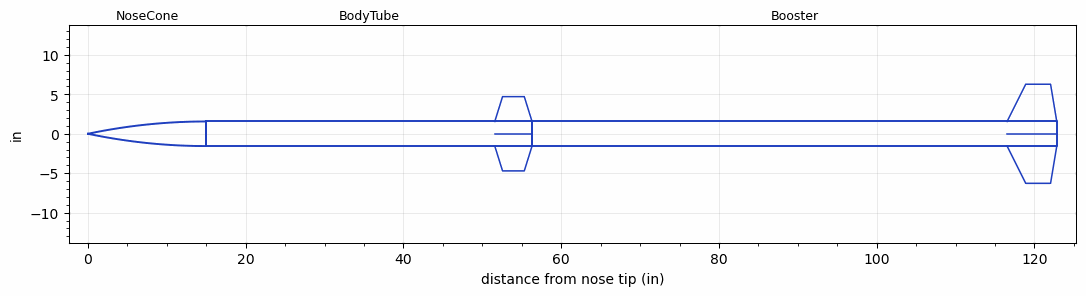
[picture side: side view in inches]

<RASAeroDocument>
 <FileVersion>2</FileVersion>
 <RocketDesign>
  <NoseCone>
   <Length>14.961</Length>
   <Diameter>3.118</Diameter>
   <Shape>Tangent Ogive</Shape>
   <Location>0</Location>
  </NoseCone>
  <BodyTube>
   <Length>41.339</Length>
   <Diameter>3.118</Diameter>
   <Location>14.961</Location>
   <Fin>
    <Count>4</Count>
    <Chord>4.724</Chord>
    <Span>3.15</Span>
    <SweepDistance>0.984</SweepDistance>
    <TipChord>2.756</TipChord>
    <Thickness>0.157</Thickness>
    <Location>4.724</Location>
    <AirfoilSection>Square</AirfoilSection>
   </Fin>
  </BodyTube>
  <Booster>
   <Length>66.535</Length>
   <Diameter>3.118</Diameter>
   <InsideDiameter>3.118</InsideDiameter>
   <Location>56.3</Location>
   <ShoulderLength>0</ShoulderLength>
   <Fin>
    <Count>4</Count>
    <Chord>6.299</Chord>
    <Span>4.724</Span>
    <SweepDistance>2.362</SweepDistance>
    <TipChord>3.15</TipChord>
    <Thickness>0.276</Thickness>
    <Location>6.299</Location>
    <AirfoilSection>Square</AirfoilSection>
   </Fin>
  </Booster>
  <Surface>Smooth (Zero Roughness)</Surface>
  <ModifiedBarrowman>False</ModifiedBarrowman>
  <Turbulence>False</Turbulence>
  <UseBooster1>True</UseBooster1>
  <UseBooster2>False</UseBooster2>
 </RocketDesign>
 <LaunchSite>
  <Altitude>0</Altitude>
  <Pressure>0</Pressure>
  <RodAngle>0</RodAngle>
  <RodLength>4</RodLength>
  <Temperature>74</Temperature>
  <WindSpeed>0</WindSpeed>
 </LaunchSite>
 <Recovery>
  <Altitude1>1000</Altitude1>
  <Altitude2>183</Altitude2>
  <DeviceType1>Parachute</DeviceType1>
  <DeviceType2>Parachute</DeviceType2>
  <Event1>True</Event1>
  <Event2>True</Event2>
  <Size1>15.98</Size1>
  <Size2>35.98</Size2>
  <EventType1>Apogee</EventType1>
  <EventType2>Altitude</EventType2>
  <CD1>0.8</CD1>
  <CD2>2.1</CD2>
 </Recovery>
 <SimulationList>
  <Simulation>
   <SustainerEngine>1/2A2  (AP)</SustainerEngine>
   <SustainerLaunchWt>7.86</SustainerLaunchWt>
   <SustainerCG>39.13</SustainerCG>
   <SustainerIgnitionDelay>0</SustainerIgnitionDelay>
   <Booster1Engine>L2200G  (AT)</Booster1Engine>
   <Booster1LaunchWt>28.32</Booster1LaunchWt>
   <Booster1SeparationDelay>0.5</Booster1SeparationDelay>
   <Booster1IgnitionDelay>0</Booster1IgnitionDelay>
   <Booster1CG>83.52</Booster1CG>
   <Booster1NozzleDiameter>3</Booster1NozzleDiameter>
   <IncludeBooster1>True</IncludeBooster1>
   <Booster2Delay>0</Booster2Delay>
   <IncludeBooster2>False</IncludeBooster2>
   <TimetoApogee>19.82029</TimetoApogee>
   <MaxAltitude>8271.797</MaxAltitude>
   <MaxVelocity>986.7897</MaxVelocity>
   <OptimumWt>11.79</OptimumWt>
   <OptimumMaxAlt>11.79</OptimumMaxAlt>
  </Simulation>
 </SimulationList>
</RASAeroDocument>
